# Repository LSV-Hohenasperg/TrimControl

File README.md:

# TrimmControl ControllerBoard
Wir haben eine elektronische Schaltung für den Ersatz des Relais-basierten Originalcontrollers
für die Bristell entwickelt.

In diesem Repository befinden sich die Planungsdaten und auch die Eagle-Projektdateien.
Mit dem Eagle-Layout haben wir bei LeitOn.de die Platinen herstellen lassen.

# Autoren
    * Wolfgang Messerschmidt
    * Markus Kuhnla

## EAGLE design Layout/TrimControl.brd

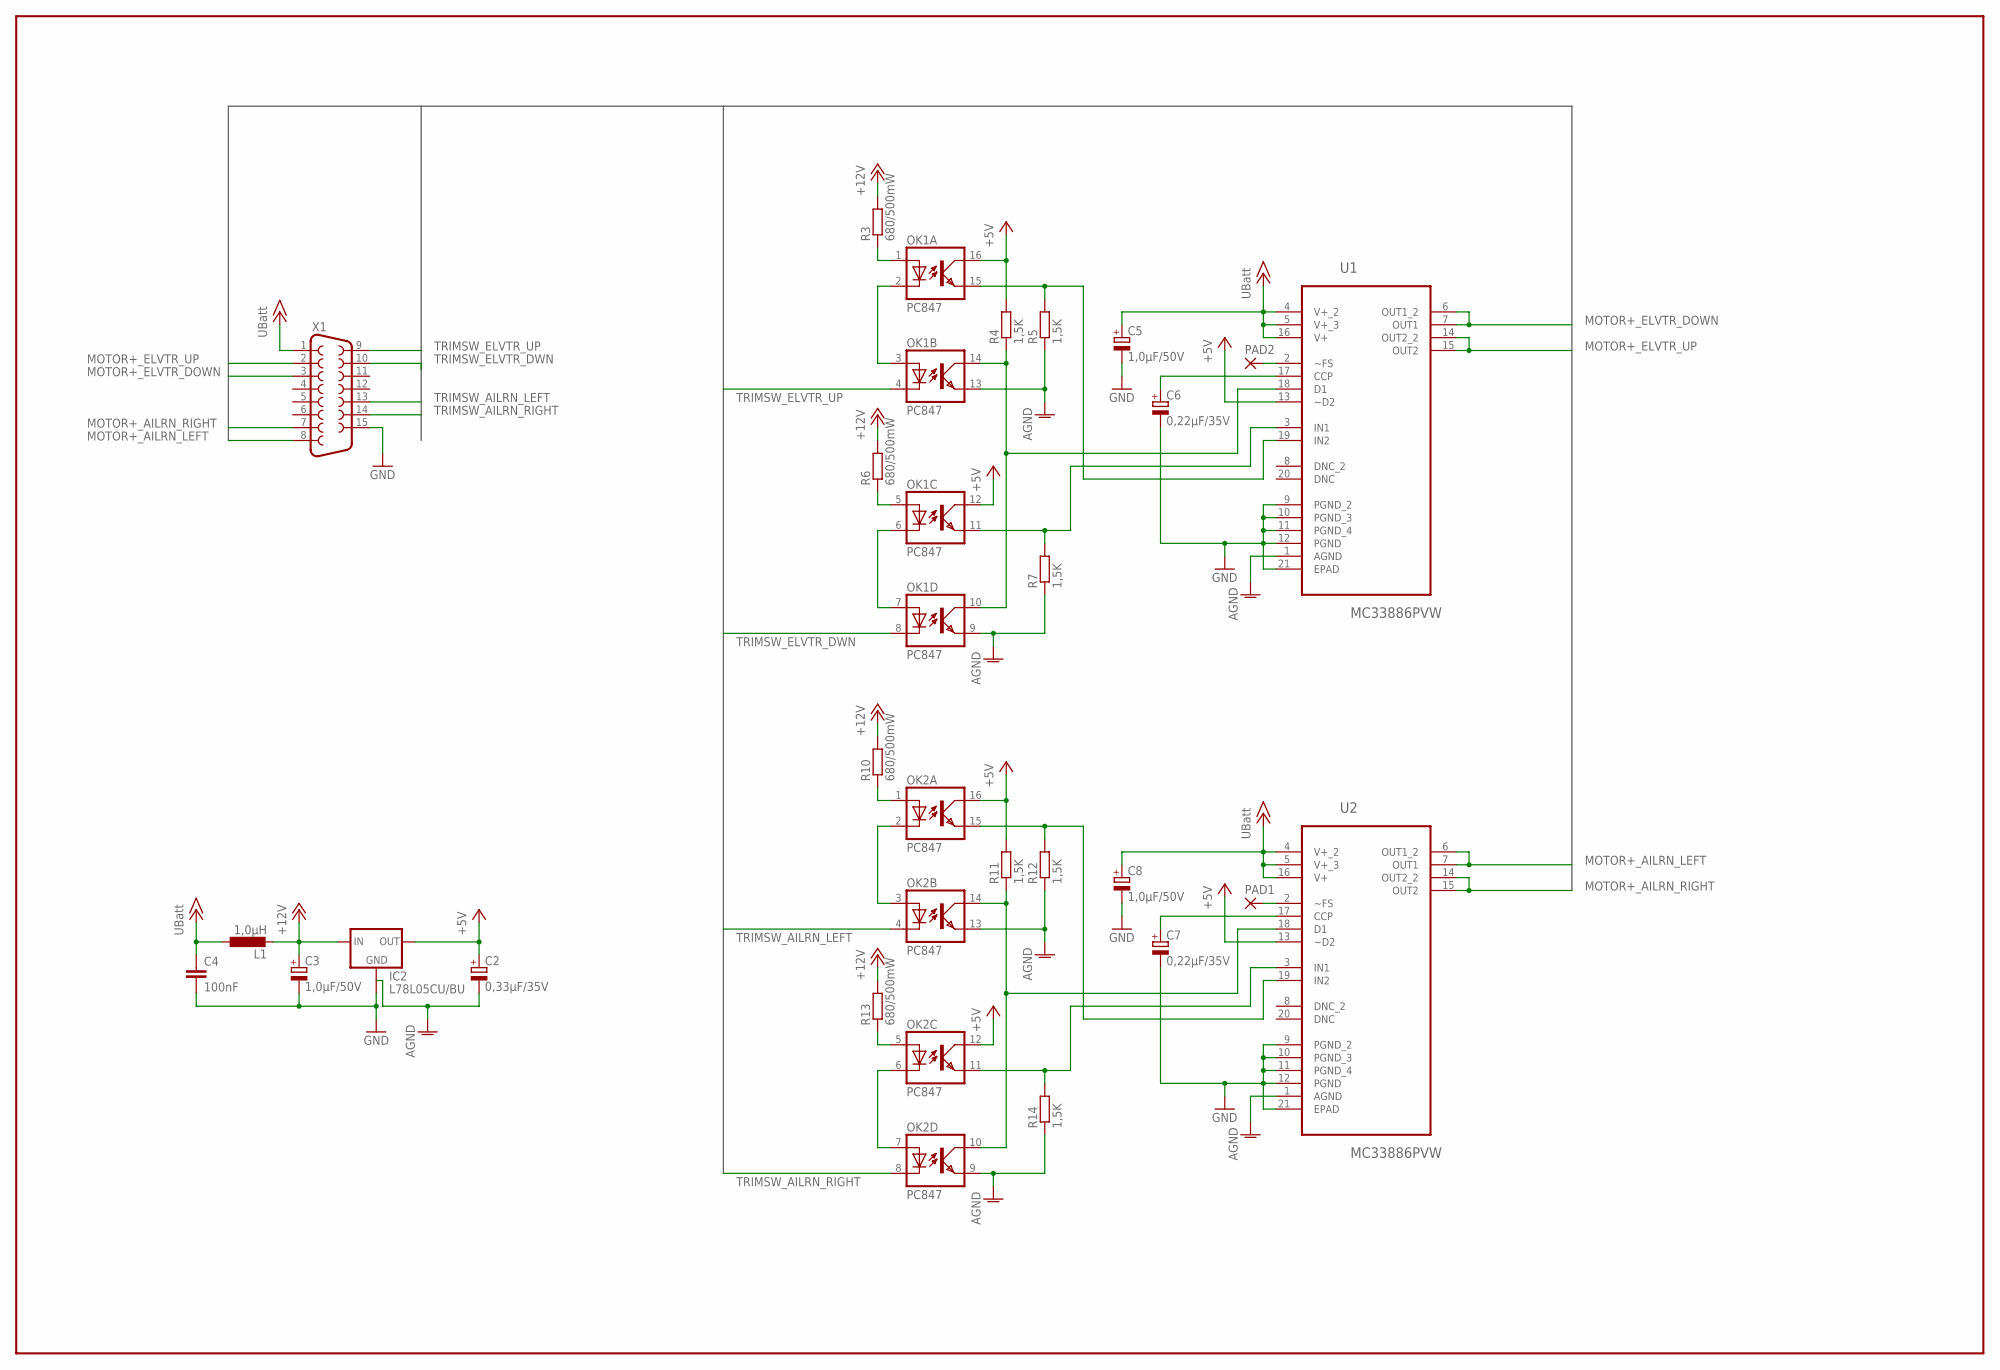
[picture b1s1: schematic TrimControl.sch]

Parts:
C2: 0,33µF/35V; A/3216-18R
C3, C5, C8: 1,0µF/50V; C/6032-28R
C4: 100nF; C0805
C6, C7: 0,22µF/35V; A/3216-18R
IC2: L78L05CU/BU; SOT89
L1: 1,0µH; L1812
OK1, OK2: PC847; DIL16
PAD1, PAD2: 1,6/0,9
R3, R6, R10, R13: 680/500mW; R1210
R4, R5, R7, R11, R12, R14: 1,5K; R0805
U1, U2: MC33886PVW; SOIC127P1420X340-21N
X1: F15HP

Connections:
+5V: C2.+, IC2.1 (OUT), OK1.12 (COL), OK1.16 (COL), OK2.12 (COL), OK2.16 (COL), R4.2, R11.2, U1.13 (~D2), U2.13 (~D2)
+12V: C3.+, IC2.3 (IN), L1.2, R3.2, R6.2, R10.2, R13.2
AGND: C2.-, IC2.2 (GND), OK1.9 (EMIT), OK1.13 (EMIT), OK2.9 (EMIT), OK2.13 (EMIT), R5.1, R7.1, R12.1, R14.1, U1.1 (AGND), U2.1 (AGND)
GND: C3.-, C4.2, C5.-, C6.-, C7.-, C8.-, IC2.4 (GND1), U1.9 (PGND_2), U1.10 (PGND_3), U1.11 (PGND_4), U1.12 (PGND), U1.21 (EPAD), U2.9 (PGND_2), U2.10 (PGND_3), U2.11 (PGND_4), U2.12 (PGND), U2.21 (EPAD), X1.15
MOTOR+_AILRN_LEFT: U2.6 (OUT1_2), U2.7 (OUT1), X1.8
MOTOR+_AILRN_RIGHT: U2.14 (OUT2_2), U2.15 (OUT2), X1.7
MOTOR+_ELVTR_DOWN: U1.6 (OUT1_2), U1.7 (OUT1), X1.3
MOTOR+_ELVTR_UP: U1.14 (OUT2_2), U1.15 (OUT2), X1.2
unnamed: C6.+, U1.17 (CCP)
unnamed: C7.+, U2.17 (CCP)
unnamed: OK1.1 (A), R3.1
unnamed: OK2.1 (A), R10.1
unnamed: OK1.10 (COL), OK1.14 (COL), R4.1, U1.18 (D1)
unnamed: PAD2.1, U1.2 (~FS)
unnamed: PAD1.1, U2.2 (~FS)
unnamed: OK1.2 (C), OK1.3 (A)
unnamed: OK1.5 (A), R6.1
unnamed: OK1.6 (C), OK1.7 (A)
unnamed: OK1.15 (EMIT), R5.2, U1.19 (IN2)
unnamed: OK2.2 (C), OK2.3 (A)
unnamed: OK1.11 (EMIT), R7.2, U1.3 (IN1)
unnamed: OK2.10 (COL), OK2.14 (COL), R11.1, U2.18 (D1)
unnamed: OK2.5 (A), R13.1
unnamed: OK2.6 (C), OK2.7 (A)
unnamed: OK2.11 (EMIT), R14.2, U2.3 (IN1)
unnamed: OK2.15 (EMIT), R12.2, U2.19 (IN2)
TRIMSW_AILRN_LEFT: OK2.4 (C), X1.13
TRIMSW_AILRN_RIGHT: OK2.8 (C), X1.14
TRIMSW_ELVTR_DWN: OK1.8 (C), X1.10
TRIMSW_ELVTR_UP: OK1.4 (C), X1.9
UBATT: C4.1, C5.+, C8.+, L1.1, U1.4 (V+_2), U1.5 (V+_3), U1.16 (V+), U2.4 (V+_2), U2.5 (V+_3), U2.16 (V+), X1.1

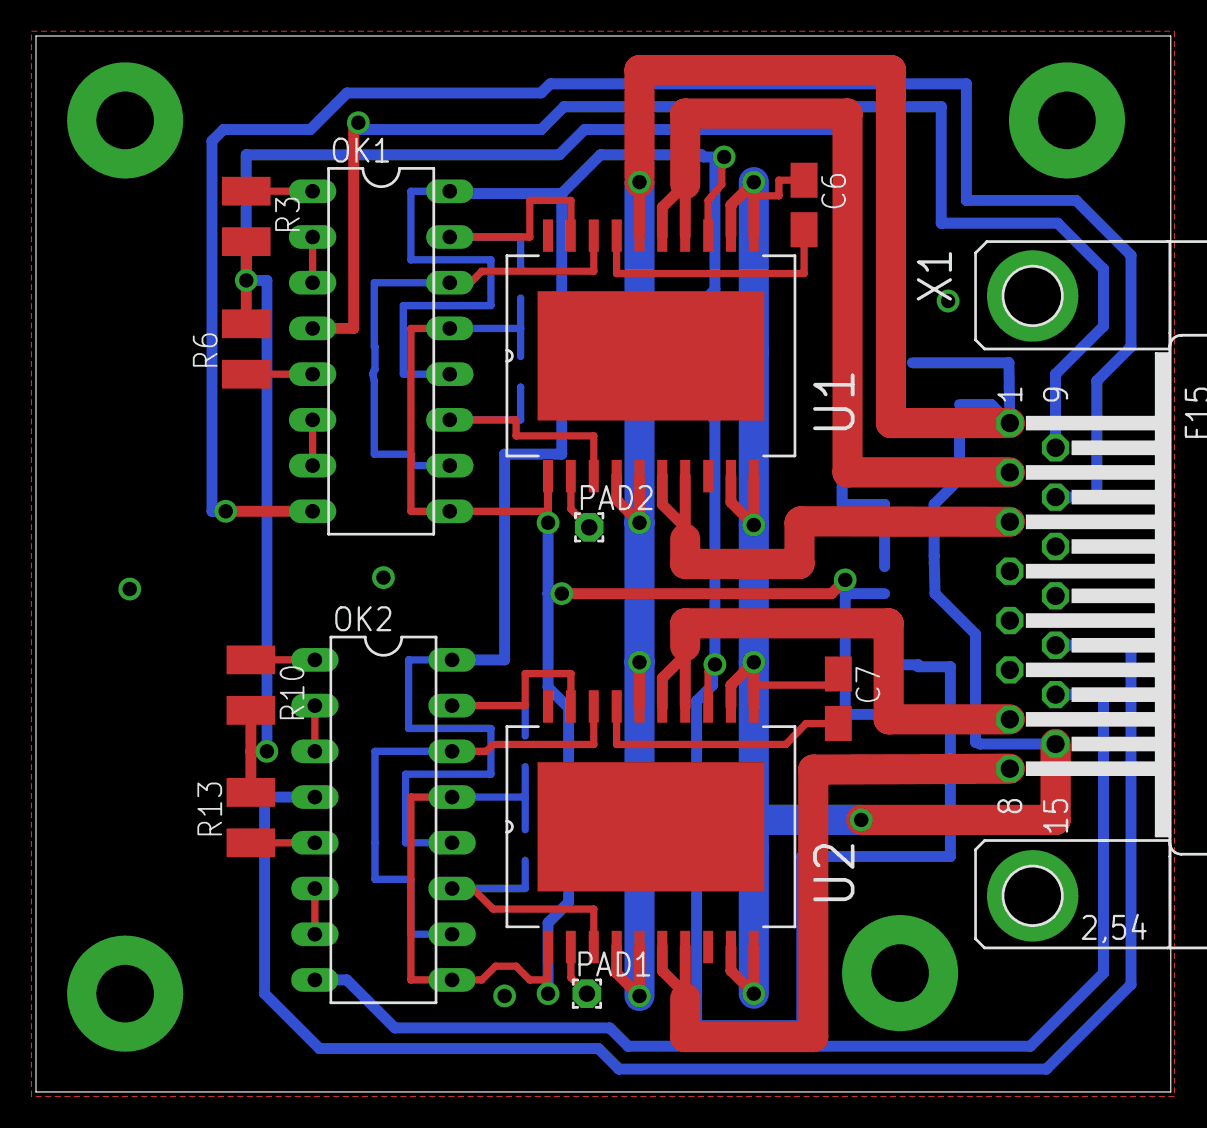
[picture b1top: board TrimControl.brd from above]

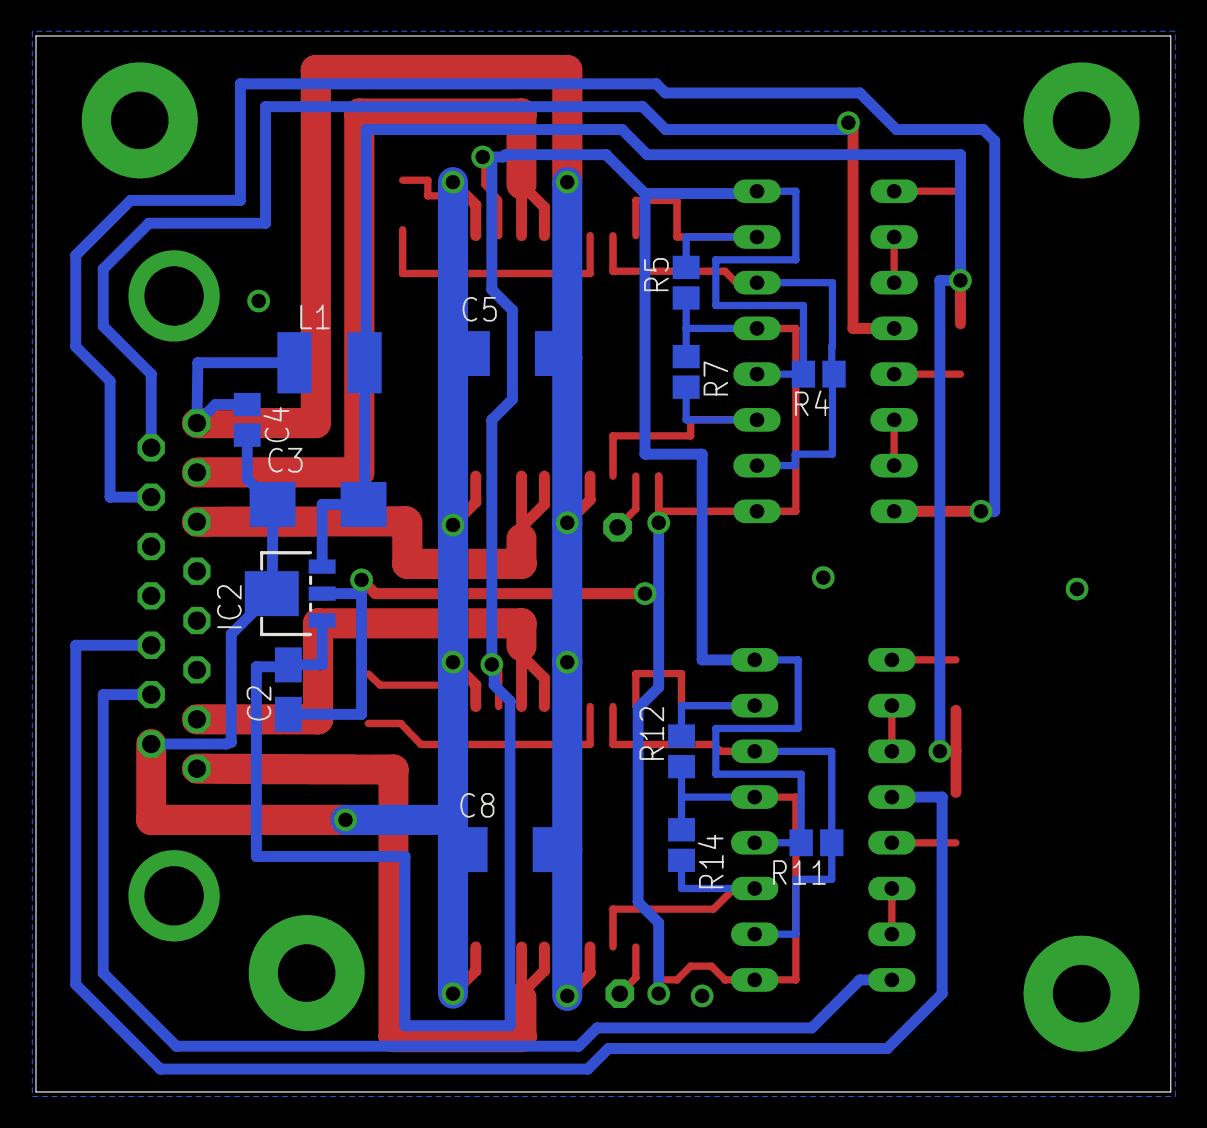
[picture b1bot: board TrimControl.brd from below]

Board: 2 copper layers, 63.0 x 58.7 mm, 26 parts (13 on the bottom side), 31 nets.

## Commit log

2019-08-29 Version, die ich von Wolfgangs Ablage importiert habe.
